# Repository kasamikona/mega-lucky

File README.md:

# Mega-Lucky
Ultimate IO mod for the Lucky Group electronic guitar toy (らっき組 ギター) RK-001, made by People Co., Ltd.  

The guitar toy in question has no external connectors. None at all, not even a headphone jack.
This project adds a 3.5mm line-out, a 6VDC barrel jack power input,
and MIDI in/out through additional 3.5mm TRS jacks.  

## Line out
The line-level audio output is amplified from the DAC output directly.
The DAC is stereo but the built-in volume pot is only mono, so I have chosen to bypass the pot for line-out.
In the future I may look into ways of including the pot without significant physical mods.
There are option jumpers to filter out the strong bass designed for the internal speaker.  

## Power
The power input intercepts the battery connector to allow external 6VDC as an alternative.
The safe range is actually 4.5 to 9 volts, but the built-in regulator will run hotter at higher voltages.
There is no overvoltage protection, but polarity protection and minimal filtering is included.  

## MIDI
The MIDI connections take advantage of some unlabeled test points on the guitar's PCB.
The guitar is based around a Yamaha XU947C0 LSI chip, which integrates a CPU and MIDI synth.
I found that its MIDI input and output pins (same pins as on a DB51XG) are fully functional.
Input may be used as a MIDI synth module combined with line-out, while output implements a basic MIDI guitar controller.
The Mega-Lucky board provides these MIDI in/out connections via type-A\* TRS connectors.  

## Installation
A proper visual installation guide will be made once the full functionality of the mod is verified.  

For now some rough steps:
- Desolder speaker wires, take the main board out.
- Remove two mixing resistors R10,R45 from the main board.
- Add two wires and optional shield to the DAC (IC3) output pins (L closest to pot).
- If reusing original battery connector, desolder it and install on mod board, otherwise use new connector.
- Use the 3D-printed drill guide to mark and drill holes (6.5-7mm for TRS, 8-9mm for DC).
- Solder the audio wires to the marked points on the mod board.
- Carefully wiggle the main board and mod connectors into place, mind the ribbon cables.
- Put M3 washers (0.5mm thick) between the boards at the screw holes and screw everything back in.
- Wire the MIDI pads to the relevant test points\*\*.
- Solder remaining 6 pads to the adjacent pads/pins.
- Resolder speaker wires or add some kind of connector.
- Solder the `HI-BASS` option jumper if desired. DO NOT set the `LOUD` jumpers on v1.0 boards.
- Solder MIDI type jumpers\* for your adapters.
- Extend the battery cable if necessary to reach the new location. Don't plug into old location.\*\*\*

\* MIDI TRS type:
Recommended type A (MIDI standard, KORG, Akai, Make Noise etc).
Alternative type B (Arturia, Novation etc).
You may need extra wire clippings to bridge the jumpers for type B on v1.0 boards.  

\*\* MIDI test points (will add photos later):
Below the big `DY798` text, the second test point down is MIDI out (to `M.TX`).
Further down are 2 more points, furthest to the right is MIDI in (to `M.RX`).  

\*\*\* Battery connector safety:
The original battery connector pads are not disconnected when external DC is used.
Using these may cause extensive damage if external DC is connected with batteries in place.
You must plug the battery cable into the new location on the mod board instead.  

## PCB assembly notes
- Clean out castellated pads with tweezers if produced the cheap way (i.e. not paying for special routing).
- Shave the top-front straight edge of the TRS connectors if new to ensure a proper fit.
- You may wish to leave some connector pins unsoldered to allow realigning during installation.
- Don't populate Q1-Q3, R25-R28, these are experimental alternative MIDI out driver.
- DO NOT set the `LOUD` jumpers on v1.0 boards, this is broken. Leave R19-R22 & C13 unpopulated.

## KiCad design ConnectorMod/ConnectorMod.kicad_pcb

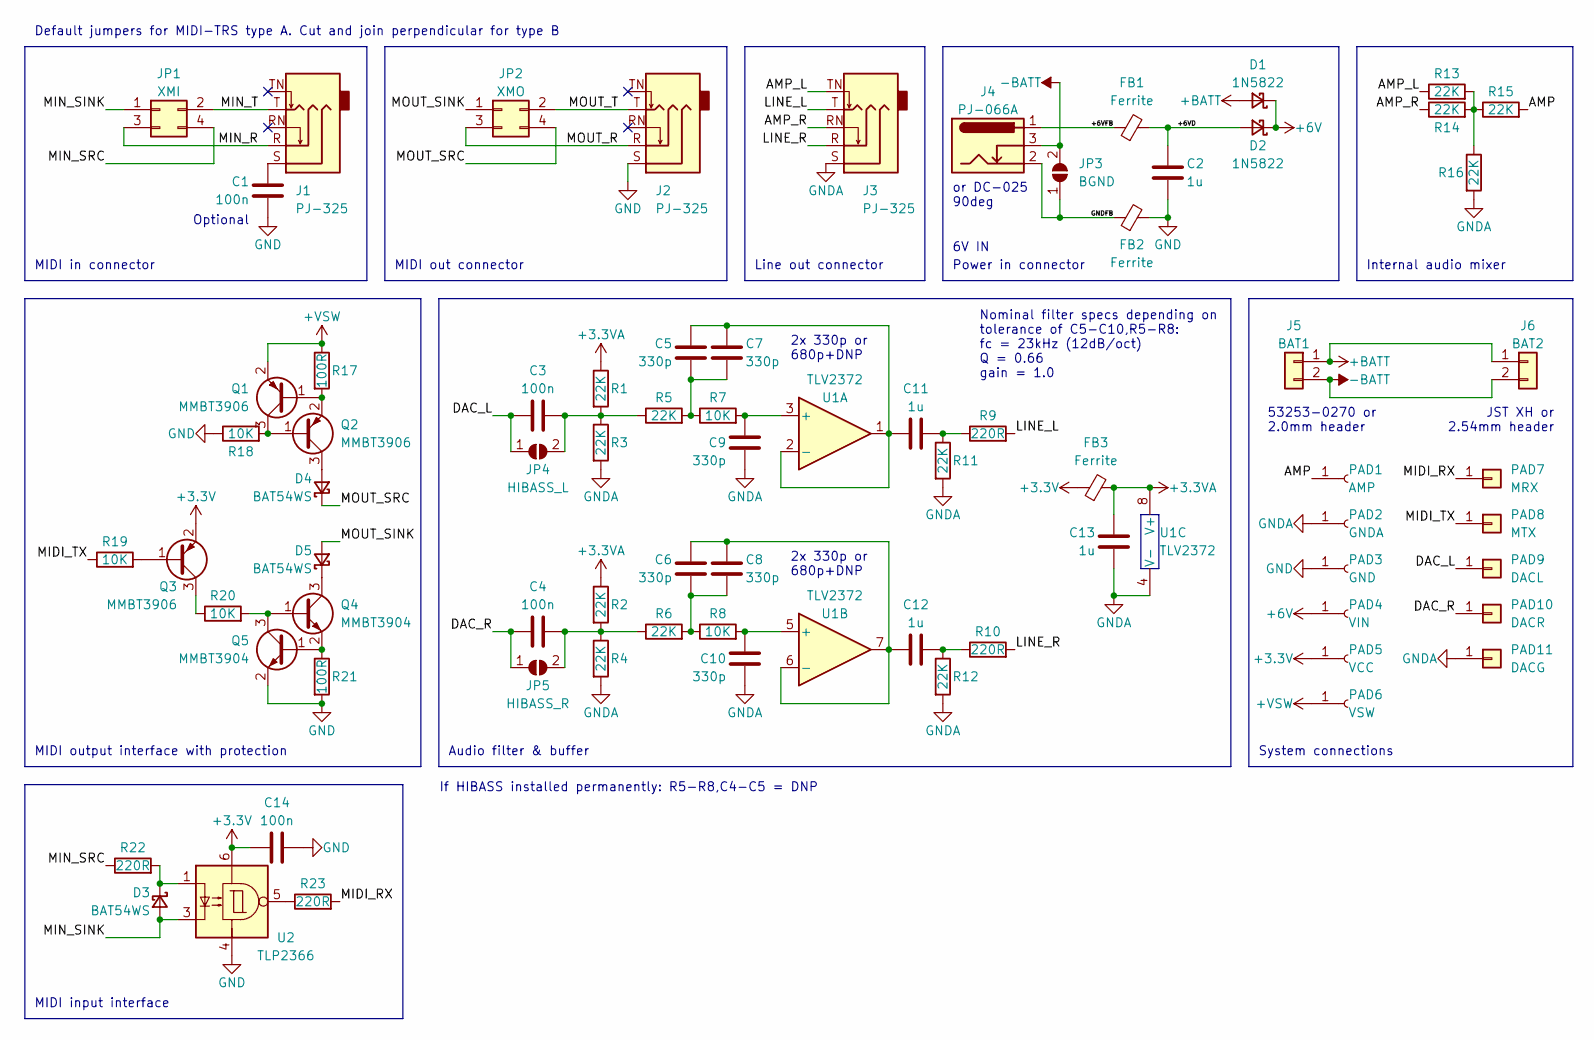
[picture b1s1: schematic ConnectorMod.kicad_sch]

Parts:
C1, C14: 100n; C_0603_1608Metric
C2, C11, C12, C13: 1u; C_0805_2012Metric
C3, C4: 100n; C_0805_2012Metric
C5, C6, C7, C8, C9, C10: 330p; C_0805_2012Metric
D1, D2: 1N5822; D_SMA
D3, D4, D5: BAT54WS; D_SOD-323
FB1, FB2, FB3: Ferrite; L_1206_3216Metric_Pad1.22x1.90mm_HandSolder
J1, J2, J3: PJ-325; PJ-325_Castellated-Edge
J4: PJ-066A
J5: BAT1; Molex_Micro-Latch_53253-0270_1x02_P2.00mm_Vertical
J6: BAT2; JST_XH_B2B-XH-A_1x02_P2.50mm_Vertical
JP1: XMI; SolderJumper_Cross
JP2: XMO; SolderJumper_Cross
JP3: BGND; SolderJumper_Custom
JP4: HIBASS_L; SolderJumper_Custom
JP5: HIBASS_R; SolderJumper_Custom
PAD1: AMP; Castellated-Pad_Custom
PAD2: GNDA; Castellated-Pad_Custom
PAD3: GND; Castellated-Pad_Custom
PAD4: VIN; Castellated-Pad_Custom
PAD5: VCC; Castellated-Pad_Custom
PAD6: VSW; Castellated-Pad_Custom
PAD7: MRX; TestPoint_Pad_D2.0mm
PAD8: MTX; TestPoint_Pad_D2.0mm
PAD9: DACL; TestPoint_THTPad_D2.5mm_Drill1.2mm
PAD10: DACR; TestPoint_THTPad_D2.5mm_Drill1.2mm
PAD11: DACG; TestPoint_THTPad_D2.5mm_Drill1.2mm
Q1, Q2, Q3: MMBT3906; SOT-23
Q4, Q5: MMBT3904; SOT-23
R1, R2, R3, R4, R5, R6, R11, R12, R13, R14, R15, R16: 22K; R_0603_1608Metric
R7, R8, R18, R19, R20: 10K; R_0603_1608Metric
R9, R10, R22, R23: 220R; R_0603_1608Metric
R17, R21: 100R; R_0603_1608Metric
U1: TLV2372; SO-8_3.9x4.9mm_P1.27mm
U2: TLP2366; SO-5_4.4x3.6mm_P1.27mm

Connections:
+3.3V: C14.1, FB3.1, PAD5.1, Q3.2 (E), U2.6
+3.3VA: C13.1, FB3.2, R1.1, R2.1, U1.8 (V+)
+6V: D1.1 (K), D2.1 (K), PAD4.1
+BATT: D1.2 (A), J5.1, J6.1
+VSW: PAD6.1, Q1.2 (E), R17.1
-BATT: J4.3, J5.2, J6.2, JP3.2 (B)
/+6VD: C2.1, D2.2 (A), FB1.2
/+6VFB: FB1.1, J4.1
/AMP: PAD1.1, R15.2
/AMP_L: J3.TN, R13.1
/AMP_R: J3.RN, R14.1
/DAC_L: C3.1, JP4.1 (A), PAD9.1
/DAC_R: C4.1, JP5.1 (A), PAD10.1
/GNDFB: FB2.1, J4.2, JP3.1 (A)
/LINE_L: J3.T, R9.2
/LINE_R: J3.R, R10.2
/MIDI_RX: PAD7.1, R23.2
/MIDI_TX: PAD8.1, R19.1
/MIN_R: J1.R, JP1.3
/MIN_SINK: D3.2 (A), JP1.1, U2.3
/MIN_SRC: JP1.4, R22.1
/MIN_T: J1.T, JP1.2
/MOUT_R: J2.R, JP2.3
/MOUT_SINK: D5.2 (A), JP2.1
/MOUT_SRC: D4.1 (K), JP2.4
/MOUT_T: J2.T, JP2.2
GND: C1.2, C2.2, C14.2, FB2.2, J2.S, PAD3.1, Q5.2 (E), R18.1, R21.2, U2.4
GNDA: C9.2, C10.2, C13.2, J3.S, PAD2.1, PAD11.1, R3.2, R4.2, R11.2, R12.2, R16.2, U1.4 (V-)
unnamed: C1.1, J1.S
unnamed: C5.2, C7.2, R5.2, R7.1
unnamed: C6.2, C8.2, R6.2, R8.1
unnamed: C11.2, R9.1, R11.1
unnamed: C12.2, R10.1, R12.1
unnamed: D3.1 (K), R22.2, U2.1
unnamed: D4.2 (A), Q2.3 (C)
unnamed: D5.1 (K), Q4.3 (C)
unnamed: C3.2, JP4.2 (B), R1.2, R3.1, R5.1
unnamed: C4.2, JP5.2 (B), R2.2, R4.1, R6.1
unnamed: Q1.1 (B), Q2.2 (E), R17.2
unnamed: Q1.3 (C), Q2.1 (B), R18.2
unnamed: Q3.1 (B), R19.2
unnamed: Q3.3 (C), R20.1
unnamed: Q4.1 (B), Q5.3 (C), R20.2
unnamed: Q4.2 (E), Q5.1 (B), R21.1
unnamed: R13.2, R14.2, R15.1, R16.1
unnamed: R23.1, U2.5
unnamed: C9.1, R7.2, U1.3 (+)
unnamed: C5.1, C7.1, C11.1, U1.1, U1.2 (-)
unnamed: C10.1, R8.2, U1.5 (+)
unnamed: C6.1, C8.1, C12.1, U1.6 (-), U1.7

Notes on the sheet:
2x 330p or 680p+DNP
Optional
Default jumpers for MIDI-TRS type A. Cut and join perpendicular for type B
Line out connector
JST XH or 2.54mm header
Audio filter & buffer
System connections
If HIBASS installed permanently: R5-R8,C4-C5 = DNP
Nominal filter specs depending on tolerance of C5-C10,R5-R8: fc = 23kHz (12dB/oct) Q = 0.66 gain = 1.0
or DC-025 90deg
Power in connector
53253-0270 or 2.0mm header
MIDI output interface with protection
MIDI input interface
MIDI in connector
MIDI out connector
6V IN
Internal audio mixer

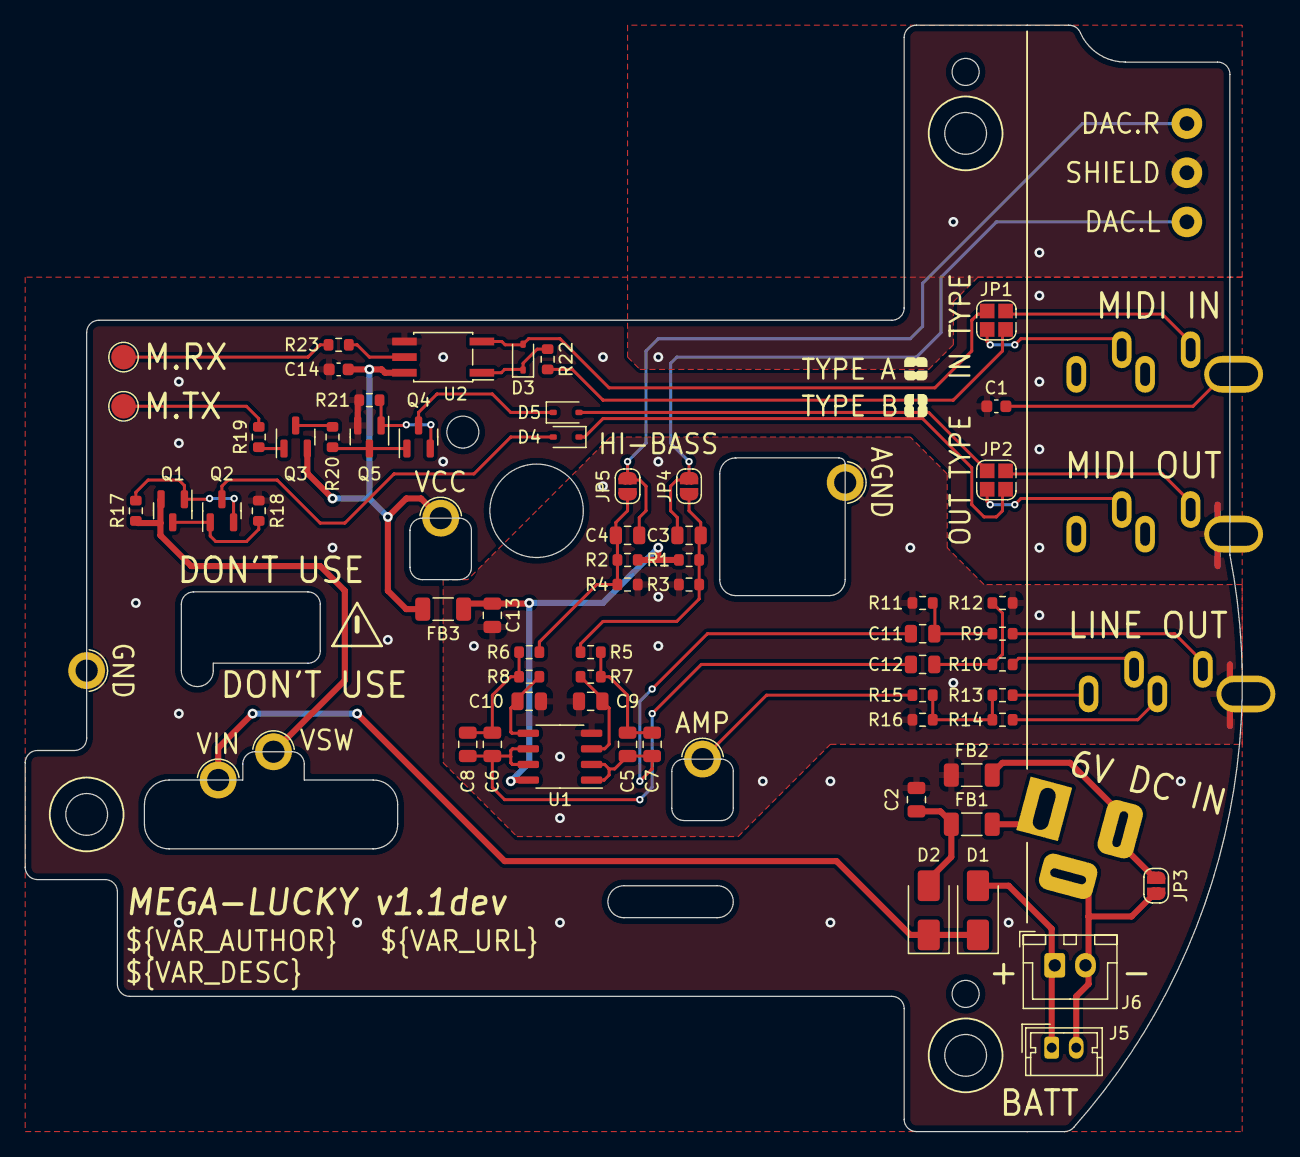
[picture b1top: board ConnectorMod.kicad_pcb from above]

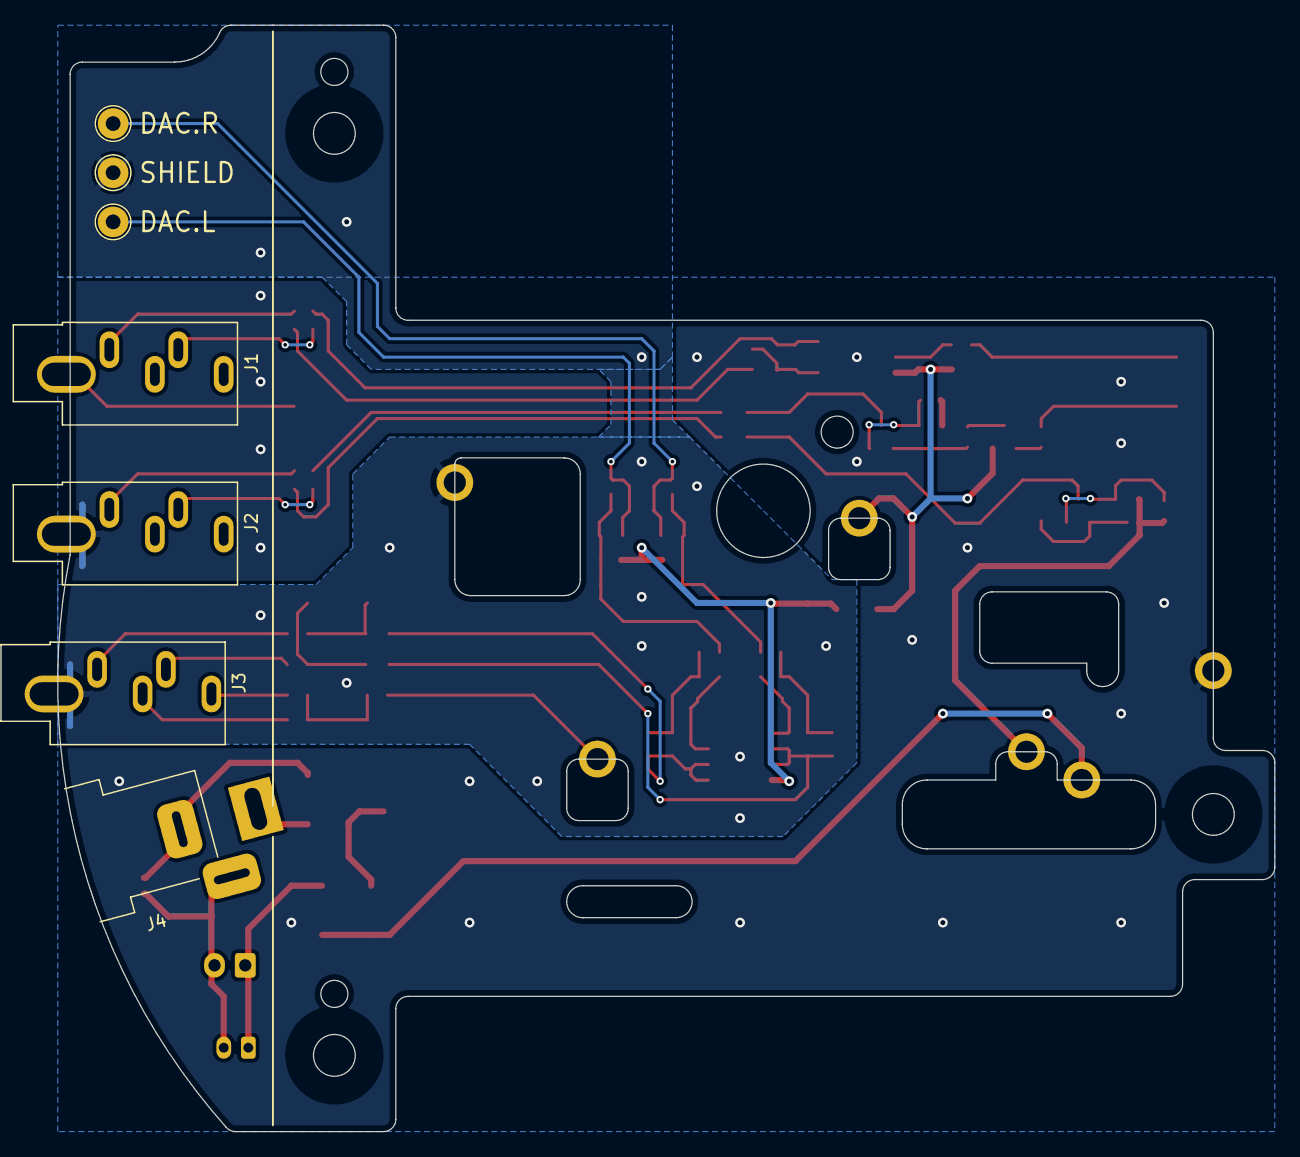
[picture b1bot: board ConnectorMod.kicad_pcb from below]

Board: 2 copper layers, 99.0 x 90.0 mm, 74 parts (7 on the bottom side), 50 nets.

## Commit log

2025-01-10 Publish v1.0 boards
2025-01-10 Add drill guide scad model
2025-01-10 Add initial readme
2025-01-11 Warn don't use loud jumpers on v1.0
2025-01-13 Remove loud jumper and tweak filter values
2025-01-13 Adjust outline and holes
2025-01-13 Change MIDI type jumpers to cross pads
2025-01-14 Use protected source/sink for MIDI out
2025-01-14 Tidy up opamp circuit
2025-01-14 Make all audio caps at least 0805
